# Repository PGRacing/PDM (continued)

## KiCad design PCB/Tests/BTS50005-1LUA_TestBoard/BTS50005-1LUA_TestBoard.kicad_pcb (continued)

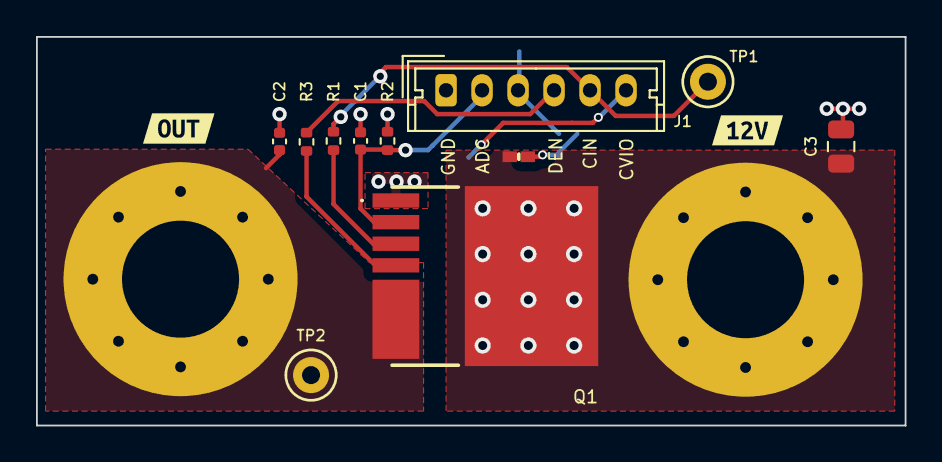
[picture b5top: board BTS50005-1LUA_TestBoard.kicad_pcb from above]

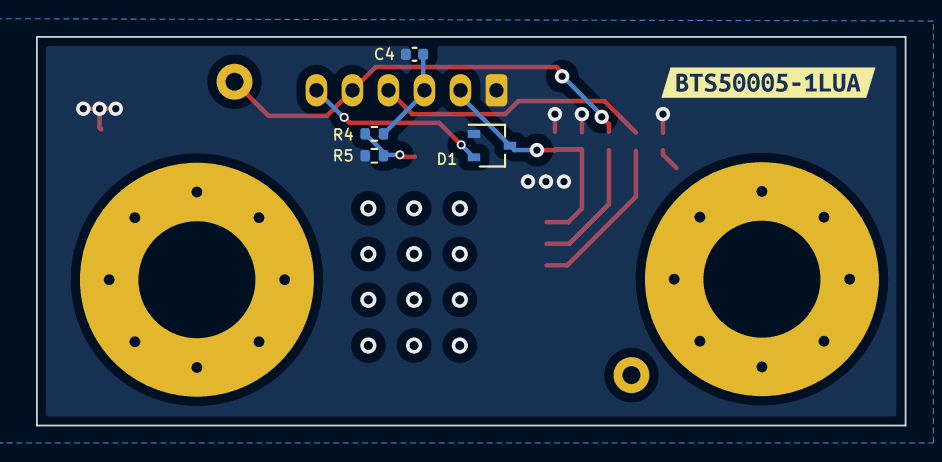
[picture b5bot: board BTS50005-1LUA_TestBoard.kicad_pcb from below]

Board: 2 copper layers, 48.3 x 21.6 mm, 20 parts (5 on the bottom side), 11 nets.

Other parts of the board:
kibuzzard-65429BC2: G***; kibuzzard-65429BC2
kibuzzard-6542993B: G***; kibuzzard-6542993B
kibuzzard-65429977: G***; kibuzzard-65429977

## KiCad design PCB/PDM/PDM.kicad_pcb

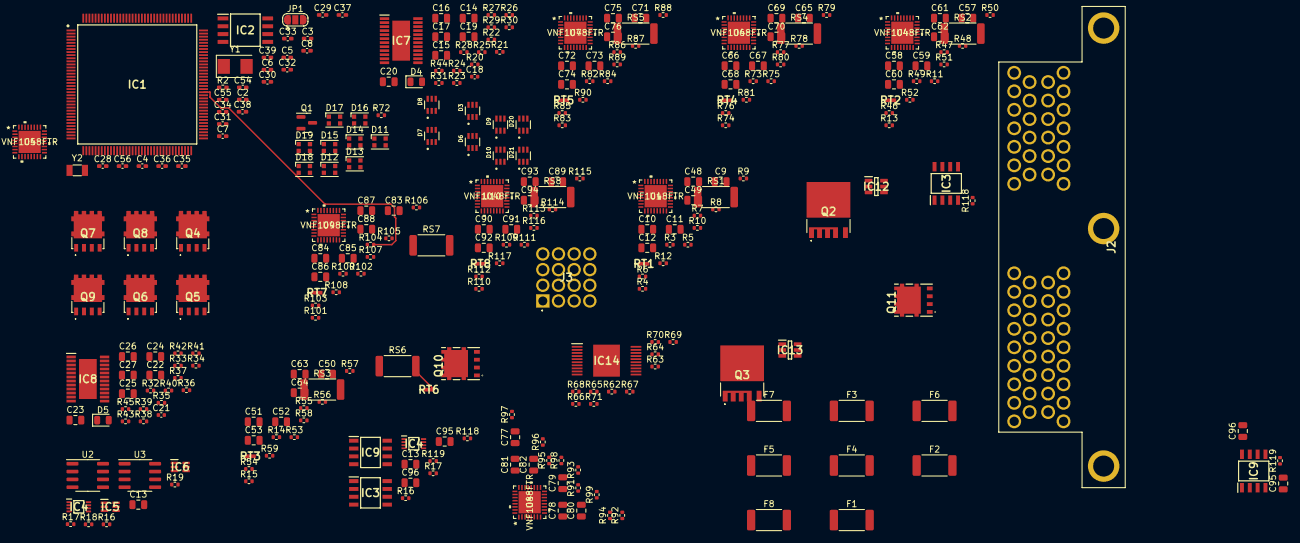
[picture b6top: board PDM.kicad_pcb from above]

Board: 2 copper layers, 294 parts (0 on the bottom side), 210 nets.

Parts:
C2: 4u7; C_0402_1005Metric_Pad0.74x0.62mm_HandSolder
C3, C7, C55, C56: 10pF; C_0402_1005Metric_Pad0.74x0.62mm_HandSolder
C4, C54: 1u; C_0402_1005Metric_Pad0.74x0.62mm_HandSolder
C5, C6, C8, C28, C29, C30, C31, C32, C33, C34, C35, C36, C37, C38, C39: 100n; C_0402_1005Metric_Pad0.74x0.62mm_HandSolder
C9, C50, C57, C65, C71, C77, C83, C89: 1uF; C_0805_2012Metric
C10, C11, C12, C19, C22, C51, C52, C53, C58, C59, C60, C66, C67, C68, C72, C73, C74, C78, C79, C80, C84, C85, C86, C90, C91, C92: 470nF; C_0805_2012Metric
C13, C96: 0,1mF; C_0805_2012Metric
C13#2, C20, C23, C49, C62, C64, C70, C76, C82, C88, C94, C95, C95#2, C96#2: 100nF; C_0805_2012Metric
C14, C15, C16, C17, C24, C25, C26, C27: 10nf; C_0805_2012Metric
C18, C21: 220pF; C_0402_1005Metric
C48, C61, C63, C69, C75, C81, C87, C93: 20uF; C_0805_2012Metric
D3, D6, D7, D8, D9, D10, D20, D21: BAT54BRW-7-F; SOT65P210X110-6N
D4, D5: 7V; D_0805_2012Metric
D11, D12, D13, D14, D15, D16, D17, D18, D19: WS2812B; LED_WS2812B-2020_PLCC4_2.0x2.0mm
F1, F2, F3, F4, F5, F6, F7, F8: 40A; Fuse_2512_6332Metric
IC1: STM32L496ZGT6; QFP50P2200X2200X160-144N
IC2: AT25SF128A-SHB-T; SOIC127P798X216-8N
IC3, IC3#2, IC9, IC9#2: SN65HVD230QDG4Q1; SOIC127P600X175-8N
IC4, IC4#2: TS5A21366DCUR; SOP50P310X90-8N
IC5, IC6: TMP126NDCKR; SOT65P210X110-6N
IC7, IC8: BTS722204ESAXUMA1; SOP65P600X115-25N
IC12, IC13: LM5050MK-1_NOPB; SOT95P280X110-6N
IC14: TLE9104SHXUMA1; SOP50P1030X260-21N
J2: 6473427-1; 64734271
J3: N01_036_6501_001; N010366501001
JP1: SolderJumper_3_Open; SolderJumper-3_P1.3mm_Open_RoundedPad1.0x1.5mm
Q1: MMBT3904; SOT-23
Q2, Q3: IAUA250N04S6N007AUMA1
Q4, Q5, Q6, Q7, Q8, Q9: STL135N8F7AG
Q10, Q11: STL225N6F7AG; POWERFLAT_5X6
R2: 1k; R_0402_1005Metric_Pad0.72x0.64mm_HandSolder
R3, R5, R6, R7, R8, R9, R11, R14, R20, R21, R22, R23, R31, R35, R36, R37, R38, R43, R44, R45, R46, R47, R48, R49, R50, R53, R54, R55, R56, R57, R64, R65, R66, R67, R70, R71, R73, R75, R76, R77, R78, R79, R82, R84, R85, R86, R87, R88, R91, R93, R94, R95, R96, R97, R100, R102, R103, R104, R105, R106, R109, R111, R112, R113, R114, R115: 1.2k; R_0402_1005Metric
R4, R13, R15, R24, R25, R26, R27, R30, R34, R39, R40, R41, R42, R62, R63, R68, R69, R74, R83, R92, R101, R110: 4.7k; R_0402_1005Metric
R10, R18, R19, R51, R58, R80, R89, R98, R107, R116: 10k; R_0402_1005Metric
R12, R52, R59, R81, R90, R99, R108, R117: 47k; R_0402_1005Metric
R16, R17, R17#2, R118: 120; R_0402_1005Metric
R16#2, R118#2, R119, R119#2: 0; R_0402_1005Metric
R28, R32: 47; R_0402_1005Metric
R29, R33: 470; R_0402_1005Metric
R72: 1k; R_0402_1005Metric
RS1, RS2, RS3, RS4, RS5, RS6, RS7, RS8: 1m; R_2512_6332Metric
RT1, RT2, RT3, RT4, RT5, RT6, RT7, RT8: B57232V5103F360; THRMC1005X60N
U1, U4, U5, U6, U7, U8, U9, U10: VNF1048FTR; QFN32L_5x5_STM
U2, U3: MCP2561-E-SN; SOIC-8_3.9x4.9mm_P1.27mm
Y1: 48Mhz; Crystal_SMD_5032-2Pin_5.0x3.2mm
Y2: 32KHz; Crystal_SMD_3215-2Pin_3.2x1.5mm

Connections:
12V_CONNECTOR: IC12.4 (IN), IC13.4 (IN), Q2.1 (S_1), Q2.2 (S_2), Q2.3 (S_3), Q2.4 (S_4), Q2.7 (S_5), Q3.1 (S_1), Q3.2 (S_2), Q3.3 (S_3), Q3.4 (S_4), Q3.7 (S_5)
+5V: D3.4, D3.5, D6.4, D6.5, D7.4, D7.5, D8.4, D8.5, D9.4, D9.5, D10.4, D10.5, D11.1 (VDD), D12.1 (VDD), D13.1 (VDD), D14.1 (VDD), D15.1 (VDD), D16.1 (VDD), D17.1 (VDD), D18.1 (VDD), D19.1 (VDD), D20.4, D20.5, D21.4, D21.5, IC14.16 (VDD), U2.3 (VDD), U3.3 (VDD)
+12V: C10.1, C48.1, C49.1, C51.1, C58.1, C61.1, C62.1, C63.1, C64.1, C66.1, C69.1, C70.1, C72.1, C75.1, C76.1, C78.1, C81.1, C82.1, C84.1, C87.1, C88.1, C90.1, C93.1, C94.1, IC12.6 (OUT), IC13.6 (OUT), Q2.6 (D), Q3.6 (D), RS1.1, RS2.1, RS3.1, RS4.1, RS5.1, RS6.1, RS7.1, RS8.1, U1.21 (ISNS_P), U1.25 (VS), U4.21 (ISNS_P), U4.25 (VS), U5.21 (ISNS_P), U5.25 (VS), U6.21 (ISNS_P), U6.25 (VS), U7.21 (ISNS_P), U7.25 (VS), U8.21 (ISNS_P), U8.25 (VS), U9.21 (ISNS_P), U9.25 (VS), U10.21 (ISNS_P), U10.25 (VS)
/BTS722204ESAXUMA1/ADC: C18.1, D4.2 (A2), R30.2
/BTS722204ESAXUMA1/OUT0: C14.1, IC7.21 (OUT0_1), IC7.22 (OUT0_2), IC7.23 (OUT0_3), IC7.24 (OUT0_4)
/BTS722204ESAXUMA1/OUT1: C15.1, IC7.19 (OUT1_1), IC7.20 (OUT1_2)
/BTS722204ESAXUMA1/OUT2: C16.1, IC7.17 (OUT2_1), IC7.18 (OUT2_2)
/BTS722204ESAXUMA1/OUT3: C17.1, IC7.13 (OUT3_1), IC7.14 (OUT3_2), IC7.15 (OUT3_3), IC7.16 (OUT3_4)
/BTS722204ESAXUMA1/VS: C20.2, IC7.25 (VS)
/BTS722204ESAXUMA2/ADC: C21.1, D5.2 (A2), R34.2
/BTS722204ESAXUMA2/OUT0: C24.1, IC8.21 (OUT0_1), IC8.22 (OUT0_2), IC8.23 (OUT0_3), IC8.24 (OUT0_4)
/BTS722204ESAXUMA2/OUT1: C25.1, IC8.19 (OUT1_1), IC8.20 (OUT1_2)
/BTS722204ESAXUMA2/OUT2: C26.1, IC8.17 (OUT2_1), IC8.18 (OUT2_2)
/BTS722204ESAXUMA2/OUT3: C27.1, IC8.13 (OUT3_1), IC8.14 (OUT3_2), IC8.15 (OUT3_3), IC8.16 (OUT3_4)
/BTS722204ESAXUMA2/VS: C23.2, IC8.25 (VS)
/HIGH SIDE1/CSN1: R11.1, R11.2, U4.2 (CSN)
/HIGH SIDE1/CSN2: R5.1, R5.2, U1.2 (CSN)
/HIGH SIDE1/CSN3: R53.1, R53.2, U5.2 (CSN)
/HIGH SIDE1/CSN4: R84.1, R84.2, U7.2 (CSN)
/HIGH SIDE1/CSN5: R75.1, R75.2, U6.2 (CSN)
/HIGH SIDE1/CSN6: R93.1, R93.2, U8.2 (CSN)
/HIGH SIDE1/CSN7: R111.1, R111.2, U10.2 (CSN)
/HIGH SIDE1/CSN8: R102.1, R102.2, U9.2 (CSN)
/HIGH SIDE1/VNF1048FTR1/MOS_GATE: Q4.4 (G), R12.2, U1.24 (HS_GATE)
/HIGH SIDE1/VNF1048FTR1/MOS_IN: Q4.5 (D_1), Q4.6 (D_2), Q4.7 (D_3), Q4.8 (D_4), Q4.9 (D_5), Q4.10 (D_6), Q4.11 (D_7), Q4.12 (D_8), Q4.13 (D_9), RS1.2, RT1.2, U1.20 (ISNS_N)
/HIGH SIDE1/VNF1048FTR1/MOS_OUT: F1.1, Q4.1 (S_1), Q4.2 (S_2), Q4.3 (S_3), R12.1, U1.23 (OUT)
/HIGH SIDE1/VNF1048FTR2/MOS_GATE: Q6.4 (G), R59.2, U5.24 (HS_GATE)
/HIGH SIDE1/VNF1048FTR2/MOS_IN: Q6.5 (D_1), Q6.6 (D_2), Q6.7 (D_3), Q6.8 (D_4), Q6.9 (D_5), Q6.10 (D_6), Q6.11 (D_7), Q6.12 (D_8), Q6.13 (D_9), RS3.2, RT3.2, U5.20 (ISNS_N)
/HIGH SIDE1/VNF1048FTR2/MOS_OUT: F3.1, Q6.1 (S_1), Q6.2 (S_2), Q6.3 (S_3), R59.1, U5.23 (OUT)
/HIGH SIDE1/VNF1048FTR3/MOS_GATE: Q7.4 (G), R90.2, U7.24 (HS_GATE)
/HIGH SIDE1/VNF1048FTR3/MOS_IN: Q7.5 (D_1), Q7.6 (D_2), Q7.7 (D_3), Q7.8 (D_4), Q7.9 (D_5), Q7.10 (D_6), Q7.11 (D_7), Q7.12 (D_8), Q7.13 (D_9), RS5.2, RT5.2, U7.20 (ISNS_N)
/HIGH SIDE1/VNF1048FTR3/MOS_OUT: F5.1, Q7.1 (S_1), Q7.2 (S_2), Q7.3 (S_3), R90.1, U7.23 (OUT)
/HIGH SIDE1/VNF1048FTR4/MOS_GATE: Q9.4 (G), R99.2, U8.24 (HS_GATE)
/HIGH SIDE1/VNF1048FTR4/MOS_IN: Q9.5 (D_1), Q9.6 (D_2), Q9.7 (D_3), Q9.8 (D_4), Q9.9 (D_5), Q9.10 (D_6), Q9.11 (D_7), Q9.12 (D_8), Q9.13 (D_9), RS6.2, RT6.2, U8.20 (ISNS_N)
/HIGH SIDE1/VNF1048FTR4/MOS_OUT: F6.1, Q9.1 (S_1), Q9.2 (S_2), Q9.3 (S_3), R99.1, U8.23 (OUT)
/HIGH SIDE1/VNF1048FTR5/MOS_GATE: Q8.4 (G), R81.2, U6.24 (HS_GATE)
/HIGH SIDE1/VNF1048FTR5/MOS_IN: Q8.5 (D_1), Q8.6 (D_2), Q8.7 (D_3), Q8.8 (D_4), Q8.9 (D_5), Q8.10 (D_6), Q8.11 (D_7), Q8.12 (D_8), Q8.13 (D_9), RS4.2, RT4.2, U6.20 (ISNS_N)
/HIGH SIDE1/VNF1048FTR5/MOS_OUT: F4.1, Q8.1 (S_1), Q8.2 (S_2), Q8.3 (S_3), R81.1, U6.23 (OUT)
/HIGH SIDE1/VNF1048FTR6/MOS_GATE: Q10.4 (G), R117.2, U10.24 (HS_GATE)
/HIGH SIDE1/VNF1048FTR6/MOS_IN: Q10.5 (D_1), Q10.6 (D_2), Q10.7 (D_3), Q10.8 (D_4), RS8.2, RT8.2, U10.20 (ISNS_N)
/HIGH SIDE1/VNF1048FTR6/MOS_OUT: F8.1, Q10.1 (S_1), Q10.2 (S_2), Q10.3 (S_3), R117.1, U10.23 (OUT)
/HIGH SIDE1/VNF1048FTR7/MOS_GATE: Q11.4 (G), R108.2, U9.24 (HS_GATE)
/HIGH SIDE1/VNF1048FTR7/MOS_IN: Q11.5 (D_1), Q11.6 (D_2), Q11.7 (D_3), Q11.8 (D_4), RS7.2, RT7.2, U9.20 (ISNS_N)
/HIGH SIDE1/VNF1048FTR7/MOS_OUT: F7.1, Q11.1 (S_1), Q11.2 (S_2), Q11.3 (S_3), R108.1, U9.23 (OUT)
/HIGH SIDE1/VNF1048FTR/MOS_GATE: Q5.4 (G), R52.2, U4.24 (HS_GATE)
/HIGH SIDE1/VNF1048FTR/MOS_IN: Q5.5 (D_1), Q5.6 (D_2), Q5.7 (D_3), Q5.8 (D_4), Q5.9 (D_5), Q5.10 (D_6), Q5.11 (D_7), Q5.12 (D_8), Q5.13 (D_9), RS2.2, RT2.2, U4.20 (ISNS_N)
/HIGH SIDE1/VNF1048FTR/MOS_OUT: F2.1, Q5.1 (S_1), Q5.2 (S_2), Q5.3 (S_3), R52.1, U4.23 (OUT)
/MCU/PWM_OUT1: D11.4 (DIN), IC1.136 (PB6)
/MCU/PWM_OUT2: IC1.135 (PB5), R72.1
BK1_IO0: IC1.65 (PE12), IC2.5 (SI(I/O0))
BK1_IO1: IC1.66 (PE13), IC2.2 (SO(I/O1))
BK1_IO2: IC1.67 (PE14), IC2.3 (~WP(I/O2))
BK1_IO3: IC1.68 (PE15), IC2.7 (~HOLD(I/O3))
BOOT0: IC1.138 (PH3-BOOT0), R2.1
CAN1_H: IC4.2 (COM1), IC4#2.2 (COM1), IC9.7 (CANH), IC9#2.7 (CANH), U2.7 (CANH)
CAN1_L: IC9.6 (CANL), IC9#2.6 (CANL), R16.1, R17.1, U2.6 (CANL)
CAN1_RX: IC1.139 (PB8), IC9.4 (R), IC9#2.4 (R), U2.4 (RXD)
CAN1_TX: IC1.140 (PB9), IC9.1 (D), IC9#2.1 (D), U2.1 (TXD)
CAN2_H: IC3.7 (CANH), IC3#2.7 (CANH), IC4.6 (COM2), IC4#2.6 (COM2), U3.7 (CANH)
CAN2_L: IC3.6 (CANL), IC3#2.6 (CANL), R17#2.1, R118.1, U3.6 (CANL)
CAN2_RX: IC1.73 (PB12), IC3.4 (R), IC3#2.4 (R), U3.4 (RXD)
CAN2_TX: IC1.74 (PB13), IC3.1 (D), IC3#2.1 (D), U3.1 (TXD)
CAN_TERMINATOR_1: IC4.7 (IN1), IC4#2.7 (IN1)
CAN_TERMINATOR_2: IC4.3 (IN2), IC4#2.3 (IN2)
CLK: IC1.63 (PE10), IC2.6 (SCK)
GND: C2.2, C3.2, C4.2, C5.2, C6.2, C7.2, C8.2, C9.1, C13.1, C13#2.1, C14.2, C15.2, C16.2, C17.2, C18.2, C20.1, C21.2, C23.1, C24.2, C25.2, C26.2, C27.2, C28.2, C29.2, C30.2, C31.2, C32.2, C33.2, C34.2, C35.2, C36.2, C37.2, C38.2, C39.2, C48.2, C49.2, C50.1, C54.2, C55.2, C56.2, C57.1, C61.2, C62.2, C63.2, C64.2, C65.1, C69.2, C70.2, C71.1, C75.2, C76.2, C77.1, C81.2, C82.2, C83.1, C87.2, C88.2, C89.1, C93.2, C94.2, C95.1, C95#2.1, C96.1, C96#2.1, D3.1, D3.2, D4.1 (A1), D5.1 (A1), D6.1, D6.2, D7.1, D7.2, D8.1, D8.2, D9.1, D9.2, D10.1, D10.2, D11.3 (VSS), D12.3 (VSS), D13.3 (VSS), D14.3 (VSS), D15.3 (VSS), D16.3 (VSS), D17.3 (VSS), D18.3 (VSS), D19.3 (VSS), D20.1, D20.2, D21.1, D21.2, IC1.16 (VSS_1), IC1.30 (VSSA), IC1.31 (VREF-), IC1.38 (VSS_2), IC1.51 (VSS_3), IC1.61 (VSS_4), IC1.71 (VSS_5), IC1.83 (VSS_6), IC1.94 (VSS_7), IC1.107 (VSS_8), IC1.120 (VSS_9), IC1.130 (VSS_10), IC1.143 (VSS_11), IC2.4 (GND), IC3.2 (GND), IC3#2.2 (GND), IC4.4 (GND), IC4#2.4 (GND), IC5.2 (GND), IC6.2 (GND), IC7.1 (GND_1), IC8.1 (GND_1), IC9.2 (GND), IC9#2.2 (GND), IC12.2 (GND), IC13.2 (GND), IC14.2 (GND_1), IC14.9 (GND_2), IC14.12 (GND_3), IC14.19 (GND_4), IC14.21 (EP), JP1.1 (A), Q1.2 (E), R16#2.1, R28.2, R31.2, R32.2, R43.2, R44.2, R45.2, R118#2.1, R119.1, R119#2.1, U1.7 (TEST1), U1.8 (TEST2), U1.13 (GND), U2.2 (VSS), U2.8 (STBY), U3.2 (VSS), U3.8 (STBY), U4.7 (TEST1), U4.8 (TEST2), U4.13 (GND), U5.7 (TEST1), U5.8 (TEST2), U5.13 (GND), U6.7 (TEST1), U6.8 (TEST2), U6.13 (GND), U7.7 (TEST1), U7.8 (TEST2), U7.13 (GND), U8.7 (TEST1), U8.8 (TEST2), U8.13 (GND), U9.7 (TEST1), U9.8 (TEST2), U9.13 (GND), U10.7 (TEST1), U10.8 (TEST2), U10.13 (GND)
MISO: IC1.88 (PG3), IC1.112 (PC11), IC1.117 (PD3), R7.1, R7.2, R47.1, R47.2, R55.1, R55.2, R77.1, R77.2, R86.1, R86.2, R95.1, R95.2, R104.1, R104.2, R113.1, R113.2, U1.4 (SDO), U4.4 (SDO), U5.4 (SDO), U6.4 (SDO), U7.4 (SDO), U8.4 (SDO), U9.4 (SDO), U10.4 (SDO)
MOSI: IC1.89 (PG4), IC1.113 (PC12), IC1.118 (PD4), R6.1, R6.2, R46.1, R46.2, R54.1, R54.2, R76.1, R76.2, R85.1, R85.2, R94.1, R94.2, R103.1, R103.2, R112.1, R112.2, U1.3 (SDI), U4.3 (SDI), U5.3 (SDI), U6.3 (SDI), U7.3 (SDI), U8.3 (SDI), U9.3 (SDI), U10.3 (SDI)
NCS: IC1.64 (PE11), IC2.1 (~CS)
unnamed: C9.2, U1.12 (V3V3)
unnamed: C10.2, U1.27 (CP)
unnamed: C11.1, U1.31 (CP1M)
unnamed: C11.2, U1.30 (CP1P)
unnamed: C12.1, U1.29 (CP2M)
unnamed: C12.2, U1.28 (CP2P)
unnamed: C19.1, R28.1
unnamed: C19.2, IC7.2 (VDD), R29.1
unnamed: C22.1, R32.1
unnamed: C22.2, IC8.2 (VDD), R33.1
unnamed: C50.2, U5.12 (V3V3)
unnamed: C51.2, U5.27 (CP)
unnamed: C52.1, U5.31 (CP1M)
unnamed: C52.2, U5.30 (CP1P)
unnamed: C53.1, U5.29 (CP2M)
unnamed: C53.2, U5.28 (CP2P)
unnamed: C57.2, U4.12 (V3V3)
unnamed: C58.2, U4.27 (CP)
unnamed: C59.1, U4.31 (CP1M)
unnamed: C59.2, U4.30 (CP1P)
unnamed: C60.1, U4.29 (CP2M)
unnamed: C60.2, U4.28 (CP2P)
unnamed: C65.2, U6.12 (V3V3)
unnamed: C66.2, U6.27 (CP)
unnamed: C67.1, U6.31 (CP1M)
unnamed: C67.2, U6.30 (CP1P)
unnamed: C68.1, U6.29 (CP2M)
unnamed: C68.2, U6.28 (CP2P)
unnamed: C71.2, U7.12 (V3V3)
unnamed: C72.2, U7.27 (CP)
unnamed: C73.1, U7.31 (CP1M)
unnamed: C73.2, U7.30 (CP1P)
unnamed: C74.1, U7.29 (CP2M)
unnamed: C74.2, U7.28 (CP2P)
unnamed: C77.2, U8.12 (V3V3)
unnamed: C78.2, U8.27 (CP)
unnamed: C79.1, U8.31 (CP1M)
unnamed: C79.2, U8.30 (CP1P)
unnamed: C80.1, U8.29 (CP2M)
unnamed: C80.2, U8.28 (CP2P)
unnamed: C83.2, U9.12 (V3V3)
unnamed: C84.2, U9.27 (CP)
unnamed: C85.1, U9.31 (CP1M)
unnamed: C85.2, U9.30 (CP1P)
unnamed: C86.1, U9.29 (CP2M)
unnamed: C86.2, U9.28 (CP2P)
unnamed: C89.2, U10.12 (V3V3)
unnamed: C90.2, U10.27 (CP)
unnamed: C91.1, U10.31 (CP1M)
unnamed: C91.2, U10.30 (CP1P)
unnamed: C92.1, U10.29 (CP2M)
unnamed: C92.2, U10.28 (CP2P)
unnamed: D11.2 (DOUT), D12.4 (DIN)
unnamed: D12.2 (DOUT), D13.4 (DIN)
unnamed: D13.2 (DOUT), D14.4 (DIN)
unnamed: D14.2 (DOUT), D15.4 (DIN)
unnamed: D15.2 (DOUT), D16.4 (DIN)
unnamed: D16.2 (DOUT), D17.4 (DIN)
unnamed: D17.2 (DOUT), D18.4 (DIN)
unnamed: D18.2 (DOUT), D19.4 (DIN)
unnamed: IC3.8 (RS), IC3#2.8 (RS), R16#2.2, R118#2.2
unnamed: IC4.1 (NO1), IC4#2.1 (NO1), R16.2, R17.2
unnamed: IC4.5 (NO2), IC4#2.5 (NO2), R17#2.2, R118.2
unnamed: IC7.3 (SO), R20.1
unnamed: IC7.4 (SI), R21.1
unnamed: IC7.5 (SCLK), R22.1
unnamed: IC7.6 (CSN), R23.1
unnamed: IC7.7 (LHI), R44.1
unnamed: IC7.8 (IN0), R24.2
unnamed: IC7.9 (IN1), R25.2
unnamed: IC7.10 (IN2), R26.2
unnamed: IC7.11 (IN3), R27.2
unnamed: IC7.12 (IS), R30.1, R31.1
unnamed: IC8.3 (SO), R35.1
unnamed: IC8.4 (SI), R36.1
unnamed: IC8.5 (SCLK), R37.1
unnamed: IC8.6 (CSN), R38.1
unnamed: IC8.7 (LHI), R45.1
unnamed: IC8.8 (IN0), R39.2
unnamed: IC8.9 (IN1), R40.2
unnamed: IC8.10 (IN2), R41.2
unnamed: IC8.11 (IN3), R42.2
unnamed: IC8.12 (IS), R34.1, R43.1
unnamed: IC9.8 (RS), IC9#2.8 (RS), R119.2, R119#2.2
unnamed: IC12.5 (GATE), Q2.5 (G)
unnamed: IC13.5 (GATE), Q3.5 (G)
unnamed: IC14.3 (IN1), R62.2
unnamed: IC14.4 (IN3), R63.2
unnamed: IC14.5 (SO), R64.2
unnamed: IC14.6 (SI), R65.2
unnamed: IC14.7 (CSN), R66.2
unnamed: IC14.8 (SCK), R67.1
unnamed: IC14.13 (RESN), R71.1
unnamed: IC14.14 (EN), R70.1
unnamed: IC14.17 (IN4), R69.2
unnamed: IC14.18 (IN2), R68.2
unnamed: JP1.2 (C), R2.2
unnamed: Q1.1 (B), R72.2
unnamed: R3.1, R4.1, U1.6 (DIAG)
unnamed: R9.1, U1.10 (HWLO)
unnamed: R10.1, RT1.1, U1.19 (NTC)
unnamed: R10.2, U1.18 (NTC_M)
unnamed: R13.1, R49.1, U4.6 (DIAG)
unnamed: R14.1, R15.1, U5.6 (DIAG)
unnamed: R50.1, U4.10 (HWLO)
unnamed: R51.1, RT2.1, U4.19 (NTC)
unnamed: R51.2, U4.18 (NTC_M)
unnamed: R57.1, U5.10 (HWLO)
unnamed: R58.1, RT3.1, U5.19 (NTC)
unnamed: R58.2, U5.18 (NTC_M)
unnamed: R73.1, R74.1, U6.6 (DIAG)
unnamed: R79.1, U6.10 (HWLO)
unnamed: R80.1, RT4.1, U6.19 (NTC)
unnamed: R80.2, U6.18 (NTC_M)
unnamed: R82.1, R83.1, U7.6 (DIAG)
unnamed: R88.1, U7.10 (HWLO)
unnamed: R89.1, RT5.1, U7.19 (NTC)
unnamed: R89.2, U7.18 (NTC_M)
unnamed: R91.1, R92.1, U8.6 (DIAG)
unnamed: R97.1, U8.10 (HWLO)
unnamed: R98.1, RT6.1, U8.19 (NTC)
unnamed: R98.2, U8.18 (NTC_M)
unnamed: R100.1, R101.1, U9.6 (DIAG)
unnamed: R106.1, U9.10 (HWLO)
unnamed: R107.1, RT7.1, U9.19 (NTC)
unnamed: R107.2, U9.18 (NTC_M)
unnamed: R109.1, R110.1, U10.6 (DIAG)
unnamed: R115.1, U10.10 (HWLO)
unnamed: R116.1, RT8.1, U10.19 (NTC)
unnamed: R116.2, U10.18 (NTC_M)
OSC32_IN: C55.1, IC1.8 (PC14-OSC32_IN), Y2.1
OSC32_OUT: C56.1, IC1.9 (PC15-OSC32_OUT), Y2.2
OSC_IN: C3.1, IC1.23 (PH0-OSC_IN), Y1.1
OSC_OUT: C7.1, IC1.24 (PH1-OSC_OUT), Y1.2
SCK: IC1.87 (PG2), IC1.111 (PC10), IC1.115 (PD1), R8.1, R8.2, R48.1, R48.2, R56.1, R56.2, R78.1, R78.2, R87.1, R87.2, R96.1, R96.2, R105.1, R105.2, R114.1, R114.2, U1.5 (SCK), U4.5 (SCK), U5.5 (SCK), U6.5 (SCK), U7.5 (SCK), U8.5 (SCK), U9.5 (SCK), U10.5 (SCK)
SPI2_CLK: IC5.4 (SCLK), IC6.4 (SCLK)
SPI2_IO: IC5.3 (SIO), IC6.3 (SIO)
TEMP1_ALERT: IC5.5 (~ALERT), R18.2
TEMP2_ALERT: IC6.5 (~ALERT), R19.1
VDD: C2.1, C5.1, C6.1, C13.2, C13#2.2, C28.1, C29.1, C30.1, C31.1, C32.1, C33.1, C34.1, C35.1, C36.1, C38.1, C39.1, C95.2, C95#2.2, C96.2, C96#2.2, IC1.17 (VDD_1), IC1.39 (VDD_2), IC1.52 (VDD_3), IC1.62 (VDD_4), IC1.72 (VDD_5), IC1.84 (VDD_6), IC1.95 (VDDIO2_1), IC1.106 (VDDUSB), IC1.108 (VDD_7), IC1.121 (VDD_8), IC1.131 (VDDIO2_2), IC1.144 (VDD_9), IC2.8 (VCC), IC3.3 (VCC), IC3#2.3 (VCC), IC4.8 (V+), IC4#2.8 (V+), IC5.6 (VDD), IC6.6 (VDD), IC9.3 (VCC), IC9#2.3 (VCC), IC14.15 (VIO), R4.2, R13.2, R15.2, R18.1, R19.2, R29.2, R33.2, R74.2, R83.2, R92.2, R101.2, R110.2, U1.1 (VSPI), U4.1 (VSPI), U5.1 (VSPI), U6.1 (VSPI), U7.1 (VSPI), U8.1 (VSPI), U9.1 (VSPI), U10.1 (VSPI)
VDDA: C4.1, C8.1, C37.1, C54.1, IC1.32 (VREF+), IC1.33 (VDDA)

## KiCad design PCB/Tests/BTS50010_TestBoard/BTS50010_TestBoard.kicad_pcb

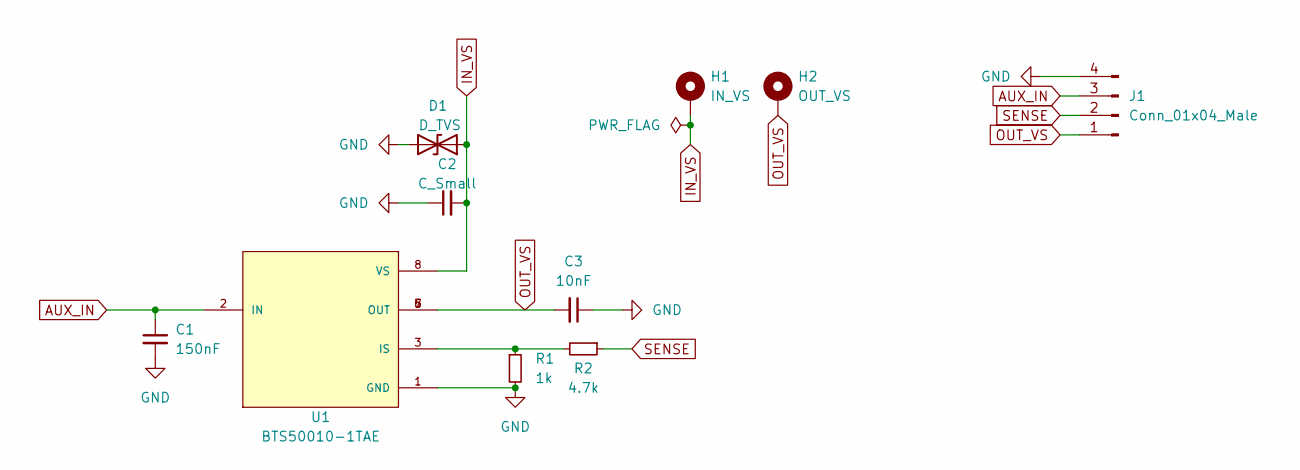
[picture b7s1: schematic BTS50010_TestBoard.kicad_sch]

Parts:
C1: 150nF; C_0805_2012Metric_Pad1.18x1.45mm_HandSolder
C2: C_Small; C_0805_2012Metric_Pad1.18x1.45mm_HandSolder
C3: 10nF; C_0805_2012Metric_Pad1.18x1.45mm_HandSolder
D1: D_TVS; D_SMA
H1: IN_VS; MountingHole_3.2mm_M3_ISO7380_Pad_TopBottom
H2: OUT_VS; MountingHole_3.2mm_M3_ISO7380_Pad_TopBottom
J1: Conn_01x04_Male; PinHeader_1x04_P2.54mm_Vertical
R1: 1k; R_0805_2012Metric_Pad1.20x1.40mm_HandSolder
R2: 4.7k; R_0805_2012Metric_Pad1.20x1.40mm_HandSolder
U1: BTS50010-1TAE; TO127P1500X440-8N; PARTREV 1.0

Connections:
AUX_IN: C1.1, J1.3, U1.2 (IN)
GND: C1.2, C2.1, C3.1, D1.2 (A2), J1.4, R1.2, U1.1 (GND)
IN_VS: C2.2, D1.1 (A1), H1.1, U1.8 (VS)
unnamed: R1.1, R2.2, U1.3 (IS)
OUT_VS: C3.2, H2.1, J1.1, U1.5 (OUT), U1.6 (OUT), U1.7 (OUT)
SENSE: J1.2, R2.1

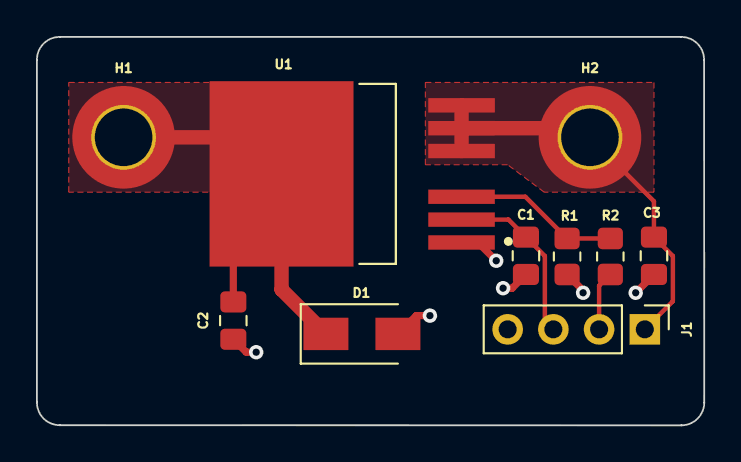
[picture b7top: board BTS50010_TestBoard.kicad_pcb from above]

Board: 2 copper layers, 37.1 x 21.6 mm, 10 parts (0 on the bottom side), 6 nets.

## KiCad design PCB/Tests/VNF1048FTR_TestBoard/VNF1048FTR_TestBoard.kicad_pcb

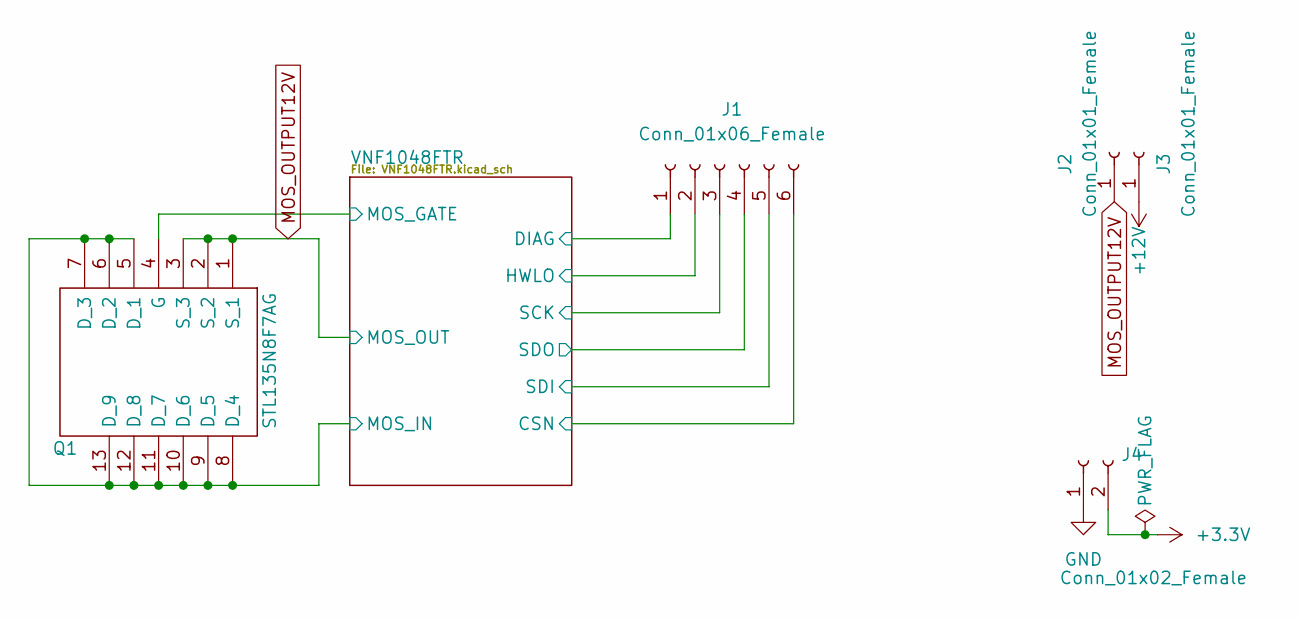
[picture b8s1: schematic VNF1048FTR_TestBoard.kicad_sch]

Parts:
J1: Conn_01x06_Female; PinSocket_1x06_P2.54mm_Vertical
J2, J3: Conn_01x01_Female; SolderWire-2sqmm_1x01_D2mm_OD3.9mm
J4: Conn_01x02_Female; PinSocket_1x02_P2.54mm_Vertical
Q1: STL135N8F7AG; Manufacturer_Part_Number STL135N8F7AG; Mouser Part Number 511-STL135N8F7AG

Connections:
+3.3V: J4.2; also elsewhere on the board
+12V: J3.1; also elsewhere on the board
/VNF1048FTR/CSN: J1.6; also elsewhere on the board
/VNF1048FTR/DIAG: J1.1; also elsewhere on the board
/VNF1048FTR/HWLO: J1.2; also elsewhere on the board
/VNF1048FTR/MOS_GATE: Q1.4 (G); also elsewhere on the board
/VNF1048FTR/MOS_IN: Q1.5 (D_1), Q1.6 (D_2), Q1.7 (D_3), Q1.8 (D_4), Q1.9 (D_5), Q1.10 (D_6), Q1.11 (D_7), Q1.12 (D_8), Q1.13 (D_9); also elsewhere on the board
/VNF1048FTR/SCK: J1.3; also elsewhere on the board
/VNF1048FTR/SDI: J1.5; also elsewhere on the board
/VNF1048FTR/SDO: J1.4; also elsewhere on the board
GND: J4.1; also elsewhere on the board
MOS_OUTPUT12V: J2.1, Q1.1 (S_1), Q1.2 (S_2), Q1.3 (S_3); also elsewhere on the board

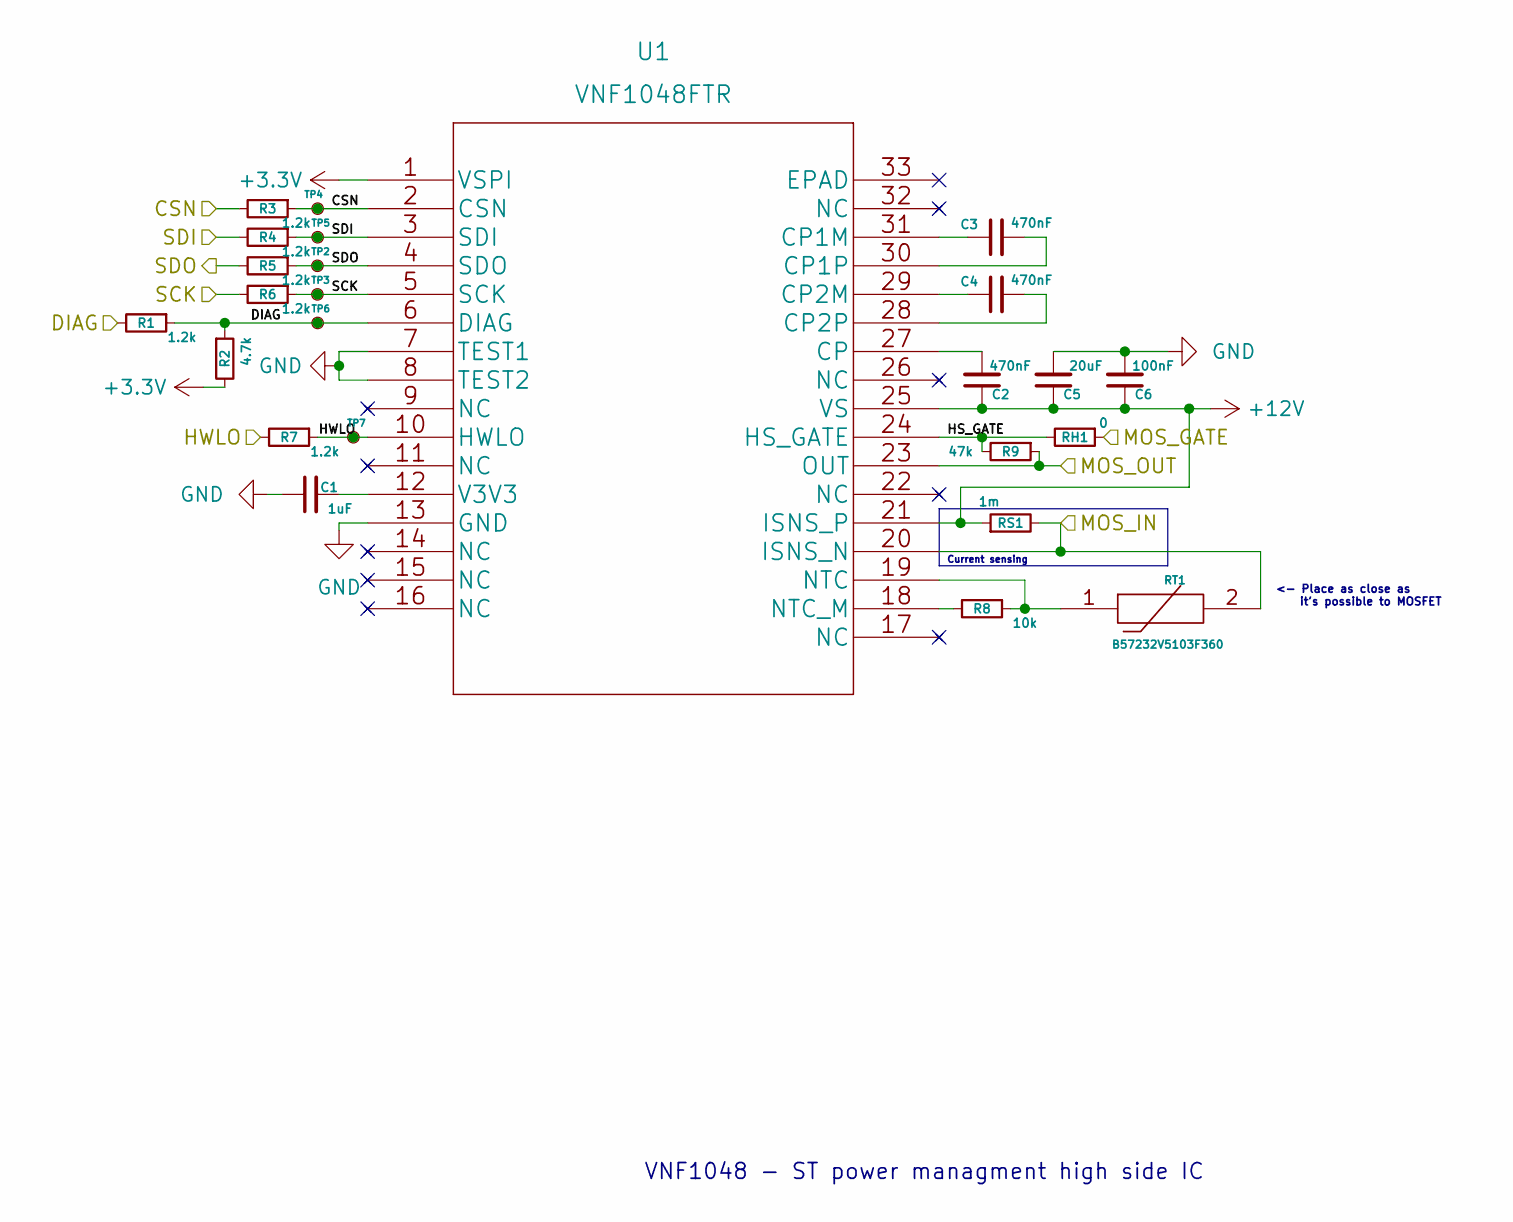
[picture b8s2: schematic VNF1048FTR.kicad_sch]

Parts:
C1: 1uF; C_0805_2012Metric
C2, C3, C4: 470nF; C_0805_2012Metric
C5: 20uF; C_0805_2012Metric
C6: 100nF; C_0805_2012Metric
R1, R3, R4, R5, R6, R7: 1.2k; R_0402_1005Metric
R2: 4.7k; R_0402_1005Metric
R8: 10k; R_0402_1005Metric
R9: 47k; R_0402_1005Metric
RH1: 0; R_Axial_DIN0204_L3.6mm_D1.6mm_P2.54mm_Vertical
RS1: 1m; R_2512_6332Metric
RT1: B57232V5103F360; THRMC1005X60N; Manufacturer_Part_Number B57232V5103F360; Mouser Part Number 871-B57232V5103F360
TP2, TP3, TP4, TP5, TP6, TP7: TestPoint_Small; TestPoint_Keystone_5000-5004_Miniature
U1: VNF1048FTR; QFN32L_5x5_STM

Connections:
+3.3V: R2.2, U1.1 (VSPI); also elsewhere on the board
+12V: C2.1, C5.1, C6.1, RS1.1, U1.21 (ISNS_P), U1.25 (VS); also elsewhere on the board
/VNF1048FTR/CSN: R3.1, R3.2, TP4.1, U1.2 (CSN); also elsewhere on the board
/VNF1048FTR/DIAG: R1.1, R1.2, R2.1, TP6.1, U1.6 (DIAG); also elsewhere on the board
/VNF1048FTR/HS_GATE: R9.2, RH1.2, U1.24 (HS_GATE)
/VNF1048FTR/HWLO: R7.1, R7.2, TP7.1, U1.10 (HWLO); also elsewhere on the board
/VNF1048FTR/MOS_GATE: RH1.1; also elsewhere on the board
/VNF1048FTR/MOS_IN: RS1.2, RT1.2, U1.20 (ISNS_N); also elsewhere on the board
/VNF1048FTR/SCK: R6.1, R6.2, TP3.1, U1.5 (SCK); also elsewhere on the board
/VNF1048FTR/SDI: R4.1, R4.2, TP5.1, U1.3 (SDI); also elsewhere on the board
/VNF1048FTR/SDO: R5.1, R5.2, TP2.1, U1.4 (SDO); also elsewhere on the board
GND: C1.1, C5.2, C6.2, U1.7 (TEST1), U1.8 (TEST2), U1.13 (GND); also elsewhere on the board
MOS_OUTPUT12V: R9.1, U1.23 (OUT); also elsewhere on the board
unnamed: C1.2, U1.12 (V3V3)
unnamed: C2.2, U1.27 (CP)
unnamed: C3.1, U1.31 (CP1M)
unnamed: C3.2, U1.30 (CP1P)
unnamed: C4.1, U1.29 (CP2M)
unnamed: C4.2, U1.28 (CP2P)
unnamed: R8.1, RT1.1, U1.19 (NTC)
unnamed: R8.2, U1.18 (NTC_M)

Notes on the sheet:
Current sensing
VNF1048 - ST power managment high side IC
<- Place as close as it's possible to MOSFET

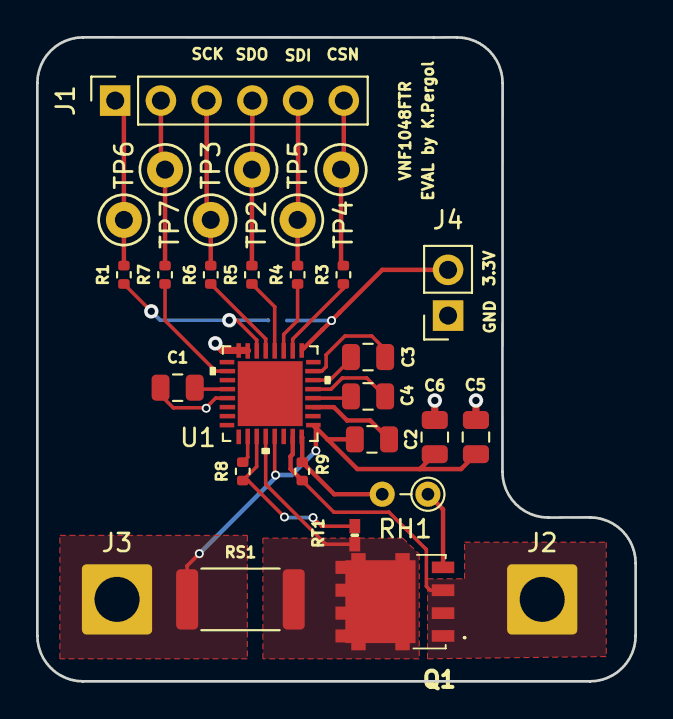
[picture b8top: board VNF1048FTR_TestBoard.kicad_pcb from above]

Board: 2 copper layers, 33.2 x 35.8 mm, 30 parts (1 on the bottom side), 21 nets.

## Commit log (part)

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2022-11-13 Added crucial elements schematics
2022-11-15 Added another high-side switch 2x7A + 2x4A SPI
2022-11-17 Added Reverse polarity protection
2022-12-31 Concept revision and MCU section changes
2022-12-31 New symbols & footprints
2022-12-31 Initial PDM mcu configuration after revision
2023-01-02 MCU preliminary scheme and qspi flash
2023-01-03 Added PWM output
2023-01-03 Added PowerMOS STL135N8F7
2023-01-03 Added new type of high side driver based on VNF1048 + STL135
2023-01-12 New test board for VNF1048FTR
2023-01-12 Minor changes in HS sechmatics
2023-01-15 Changed MCP2561 to SN65HVD230 for Q1 and 3.3V supply
2023-01-15 VNF1048FTR TestBoard pcb layout change
2023-01-15 Configured PWM_OUT2
2023-01-15 Added TE Superseal 1.0 connector 60 pins
2023-02-11 Modified test board + gerbers
2023-02-11 Modfied test board + gerbers
2023-02-28 Added adc protection and HC header radsock
2023-03-05 Modified layout
2023-03-21 New C-Lion project for L475 evaluation board
2023-03-21 Modified VNF1048 read, but SPIERROR bit is HIGH
2023-03-21 Added todo for unlock method
2023-03-21 Added status and error typedef
2023-03-21 Changed SPI options
2023-03-21 Added new vnf_unlock - spi signal seems ok\
2023-03-22 Added HWLO unlock still not working
2023-03-29 Watch dog toggled on timer - works ok - problem with unlock
2023-04-12 Current status - still SPIE problem
2023-04-12 Minor changes
2023-04-26 Modified F746 code - still SPIE error
2023-04-26 Modified L475 and ported to F746
2023-04-26 Added MCU section
2023-04-27 PDMS schematic update
2023-05-01 Schematic refactoring
2023-05-01 Added ADC overvoltage protection
2023-05-01 Added CAN ESD protection
2023-05-04 Full imu schematics
2023-05-04 Modified power switch section - partly finished
2023-05-05 Finished powerswitch section
2023-05-05 Added NTC section with 8-to-1 multiplexer
2023-05-06 Wired IMU on schematics
2023-05-06 Modified L496 .ioc
2023-05-06 Changed symbol and footprint of LM74700
2023-05-06 Removed backup files
2023-05-06 Removed backup files 2
2023-05-07 Wired all peripherals
2023-05-07 Changed power section symbol library
2023-05-09 Modified initial .ioc
2023-05-10 Mostly assigned footprints
2023-05-11 Added connector and more
2023-05-11 Added voltage mux section & layouting high side - hp
2023-05-11 HS section layout
2023-05-16 Main connector footprint update
2023-05-16 Added SATURN PCB calculations for trace width and cooper weight
2023-05-17 Imported 3.3V section with problematic shitty plugin
2023-05-17 Layout of high current traces to connector changed
2023-05-18 ADC protection layout
2023-05-20 Added Low power traces layout '4mm'
2023-05-20 Iternational update
2023-05-20 Update commit
2023-05-20 Voltage mux finished
2023-05-21 Flash layout
2023-05-21 IMU layout
2023-05-21 12V radsok connector + flash fix
2023-05-21 Oscillator layout - whole MCU
2023-05-21 Before MCU layout
2023-05-21 Partialy finished layout with 90 deg MCU
2023-05-21 Rotated MCU update
2023-05-24 Sub 99 tracks left
2023-05-24 Safety section - 74
2023-05-24 Safety finished - 53
2023-05-25 PCB finished
2023-05-27 Final touch before PCB order
2023-05-27 Via stiching +124 via on 12V plane
2023-05-28 Sitched via side
2023-05-31 Changed main power connector, added USB-C, added BLE - not wired yet
2023-05-31 USB-C symbol changed
2023-06-01 Added BLE module
2023-10-06 Adding project for VS code (PDMS)
2023-10-06 Minor chnages
2023-10-06 Added output handling basics + gitingore build files
2023-10-07 WIP on input section
2023-10-08 WIP: Added logic module
2023-10-08 WIP: Input -> Logic -> Output working example
2023-10-27 WIP logic exp
2023-10-28 Simple voltage multiplexer driver
2023-10-29 Logic form changed + vmux test
2023-10-29 Working logic + working mux (assert disabled)
2023-10-31 Minor changes in annotations
2023-10-31 Changes in Clion projects
2023-11-01 Added thermal via for BTS50005 + Gerbers
2023-11-18 Added NTC for evaluation board
2023-11-29 Adding SPI driver
2023-12-13 Simplified output batching
2023-12-13 Changed direct io to id reference
2023-12-23 PWM control for output's - NT
2023-12-28 PWM control tested
2023-12-28 Added fuse output for sensors
2024-01-10 Major changes with new switch
2024-01-13 Centered HP section
2024-01-21 PCB - Low power mosf voltage mux
2024-01-21 IMPORTANT! Batching all IS pin to single ADC peripheral
2024-02-14 Finished 2024 version + gerbers
2024-02-15 !ORDERED VERSION! - Added stiching on single channel traces
2024-02-17 Clean-up of schematics
2024-03-26 Integration of BTS72220 on HAL SPI driver
2024-03-28 Added descriptors for SPOC2 new functions
2024-03-31 Not working version of pooling multiple channel ADC
2024-04-14 !!! LAST CODE COMMIT BEFORE PINOUT CHANGE !!!
2024-04-15 Working example PCB v4.2
2024-04-15 Working mux on all 16 channels
2024-04-19 Caseing files
2024-04-19 Typo in macro usage
2024-04-20 WIP BTS500 diagnosis - non tested
2024-04-21 Added CAN telemetry + modified OC protection
2024-05-19 Last commit before adding fuses
2024-05-19 Added fuses to main output channels
2024-05-20 Added bigger LDO with lower Rth(ja), TVS suppressor diode
2024-06-04 Minor code changes
2024-06-12 Added new simplified logic handler
2024-06-22 First engine startup
2024-06-23 Added SPOC2 device simple diagnostics
2024-07-26 After FSA 2024
2024-09-04 CODE COMMIT: After all 2024 competitions
2024-09-08 Ver 4.2 ready + BTS50025 test board
2024-09-12 Changed main clock from 16Mhz to 80Mhz, timers, vmux, iwdg adjusted, channels protection and pwm not tested
2024-09-12 Adjusted PWM freq prescaler - not tested!
2024-09-23 Added safety docs
2024-09-25 Major code rework, fixing macros without proper protections, adding comments and static keywords, void args for empty argument list
2024-10-11 MP4322 Initial layout
2024-11-03 Created reverse polarity evaluation board
2024-12-15 Finished MP4322 evaluation board
2024-12-15 Added reverse-polarity board gerbers
2025-03-20 WIP New output channel diagnosing method, changed PWM implementation 175Hz (tested), added UVLO, added minimal voltage to start processing protection, added frequent device restart protection
2025-03-22 WIP PCB folder structure and schematic clean-up
2025-03-22 Generated production files for RP_MPQ5850 & MP4322 schematic change
2025-03-22 Proposed new way of project building via makefile system, created README file including build and debug instructions
2025-03-22 Fixed unaligned pointer on packed struct warning, updated README.md
2025-03-22 Add devcontainer
2025-03-22 Added seperate ADC handler file, moved initialization to init function in PDM file
2025-03-22 Fixed on-start UVLO handler
2025-03-22 Added 100ms back-off on CAN TX startup
2025-03-23 Major rebuild of can handler module, added configuration structs to modules
2025-03-27 Fixed invalid pointer to arrays - mistake with operator precedence
2025-03-27 Added BSP layer for inputs, changed FW architecture (input value evaluted on ISR)
2025-03-27 Added BTS500 fault level check based on raw adc data
2025-03-30 WIP New OC strategy
2025-03-30 setup debug from devcontainer
2025-03-30 New software oc protection implementation - not tested, not configured; modified out status enum values, modified out config and reg struct
2025-03-30 Changed ADC mode to DiscontinuousConvMode
2025-03-30 Fix - Added timer delete function on UVLO timer
2025-04-01 Modified retry logic to operate on simple compare, rather than os timers (not tested yet)
2025-04-20 Last board commit before switch to Kicad 8.0.x
2025-04-20 WIP I2t protection
2025-04-22 PDMS PCB input modification WIP - no supply
2025-04-23 Fixed memory and aux routing, fixed decoupling of MCU, fixed hse oscilator layout, fixed BTS500 input capacitors size and thermal, fixed via stiching on output channels, changed LP mos traces to thin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
2025-04-26 PDMS PCB WIP modification - finished LDO layout
2025-04-28 PDMS PCB WIP modification - fixed zones and stiching between output channel layers, DRC errors clean-up
2025-04-28 PDMS PCB WIP modification - added better input protection on battery voltage measurement point
2025-04-28 PDMS PCB WIP modification - added TVS diode and debouncing cap on safety line
2025-04-29 PDMS PCB V4.3 modification finished layout - drc clean-up, added external one-wire temp probe
2025-05-29 Added v4.2 pinout
2025-06-12 Add section
2025-07-04 2025 housing finalized
2025-07-10 Working version before competition 2025
2026-05-05 2026 dyno update
2026-05-15 Increased current readout frequency to 10kHz, added core temp readout (invalid)
2026-05-16 Added CAN virtual outputs
2026-05-16 Removed obsolete TODO's
2026-05-17 Fixed can input conversion bug for boolean, added documentation for bsp_input and input modules [NOT TESTED]
2026-05-17 Fixed ADC IRQ yield from semaphore bug, changed ADC handlers priority to higher [NOT TESTED]
2026-05-17 Changed adc1 task priority to realtime, fixed invalid SW oversampling value, added TODO for median filter in current sense [NOT TESTED]
2026-05-18 Validated bsp_phy inputs changes, fixed telemetry output for SPOC2 device, validated ADC priority change [TESTED]
2026-05-20 Added median filter - it's too slow 2.5ms processing
2026-05-21 Updated gitignore
2026-05-21 Clean-up of pdm config tool
2026-05-22 Added iso-tp with v1.6.0 revision checked out
2026-05-22 Added save to device (via CAN) capability to desktop tool
2026-05-22 Added possibility to reset device over CAN
2026-05-25 Working import and export of configuration to desktop PDMS
2026-05-28 Updated input interpretation load
2026-06-04 Release 1.0.0 of PDMS app
2026-06-04 Moved PDMS desktop tool to respective folder
2026-06-04 Removed solidworks temporary files
2026-06-04 Added glb and .step of final assembly
2026-06-04 Added xls file with Mouser PDMS v4.3 suplementary order
2026-06-05 Fixed and verified Act-on-safety-line mechanism, added PWM configuration via desktop app
2026-06-05 Added PWM setup to desktop app
2026-06-06 Added temperature TMP126 sensor handling
2026-06-07 Reduced telemetry frequency to cover underrun due to too long transmission time
2026-06-07 Added anit-aliasing filter on Vout - VMux
2026-06-08 Add IMU ASM330LHH handler
2026-06-08 Updated I2C imu speed mode to fast-mode
2026-06-08 Verified if BATCH output works correct and applied fixes
2026-06-08 Modified desktop app for batch handling
2026-06-11 WIP PWM current measurement accuracy fix: - Changed TIM3->TIM8 as PWM control - TIM8 channel 6 used as reference for ADC injected channel (ARR = 0, center of high state of PWM) - TIM8 configured as c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
2026-06-11 Batch handling fix, ISO-TP modified
2026-06-11 Fixed PWM channels alignment, added configuration of ADC-PWM channels on-the fly, fixed flash erase and prog error
2026-06-11 Fixed action on hard-fault and error handler
2026-06-11 Added soft-start functionality
2026-06-11 Added soft-start capability
2026-06-11 Added kalman to remove noise from plot
2026-06-11 Added auto-loading strategy
2026-06-12 Minor fixes after review + UVLO fix
2026-06-12 Works, control tab disabled
2026-06-12 Fixed PWM control
2026-06-12 Added I2t support for configuration, Added RMS current measurement and calculation to telemetry output
2026-06-13 Added working control tab
2026-06-13 Fixed always on
2026-06-15 Fixed I2t treshold size
2026-06-15 Additional I2t fuse chart
2026-06-15 Minor change of labels
2026-06-16 Added diagnostics data to dashboard
2026-06-17 Added external triggered inrush source
2026-06-17 Added fix on diff
2026-06-17 Added cooling factor for I2t protection
2026-06-17 Added device selection option + menu bar
2026-06-17 Added pin assigment and location
2026-06-19 Added HW filter on CAN, only for needed frames
2026-06-20 - Added verification of config diff based on hash - Fixed always on path - Fixed warning display - Added CRC32 to the end of configuration
2026-06-22 Added current PWM duty cycle to telemetry data
2026-06-22 Added duty cycle to dashboard
